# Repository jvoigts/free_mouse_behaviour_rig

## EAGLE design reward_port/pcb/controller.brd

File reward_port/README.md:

# DEPRECATED

free_mouse_behaviour_rig

i2c bus
reward port led
2 pushbuttons
nema 17 linear motor
IR led and reveicer
12V to 5V/3.3V regulators
some sort of beeper
attiny microcontroller attiny88 seems good

NEMA connector:
standard plug from 3d printer

Ring-topology connector:
GND
12VDC
i2c clk
i2c dat

Programming connector:

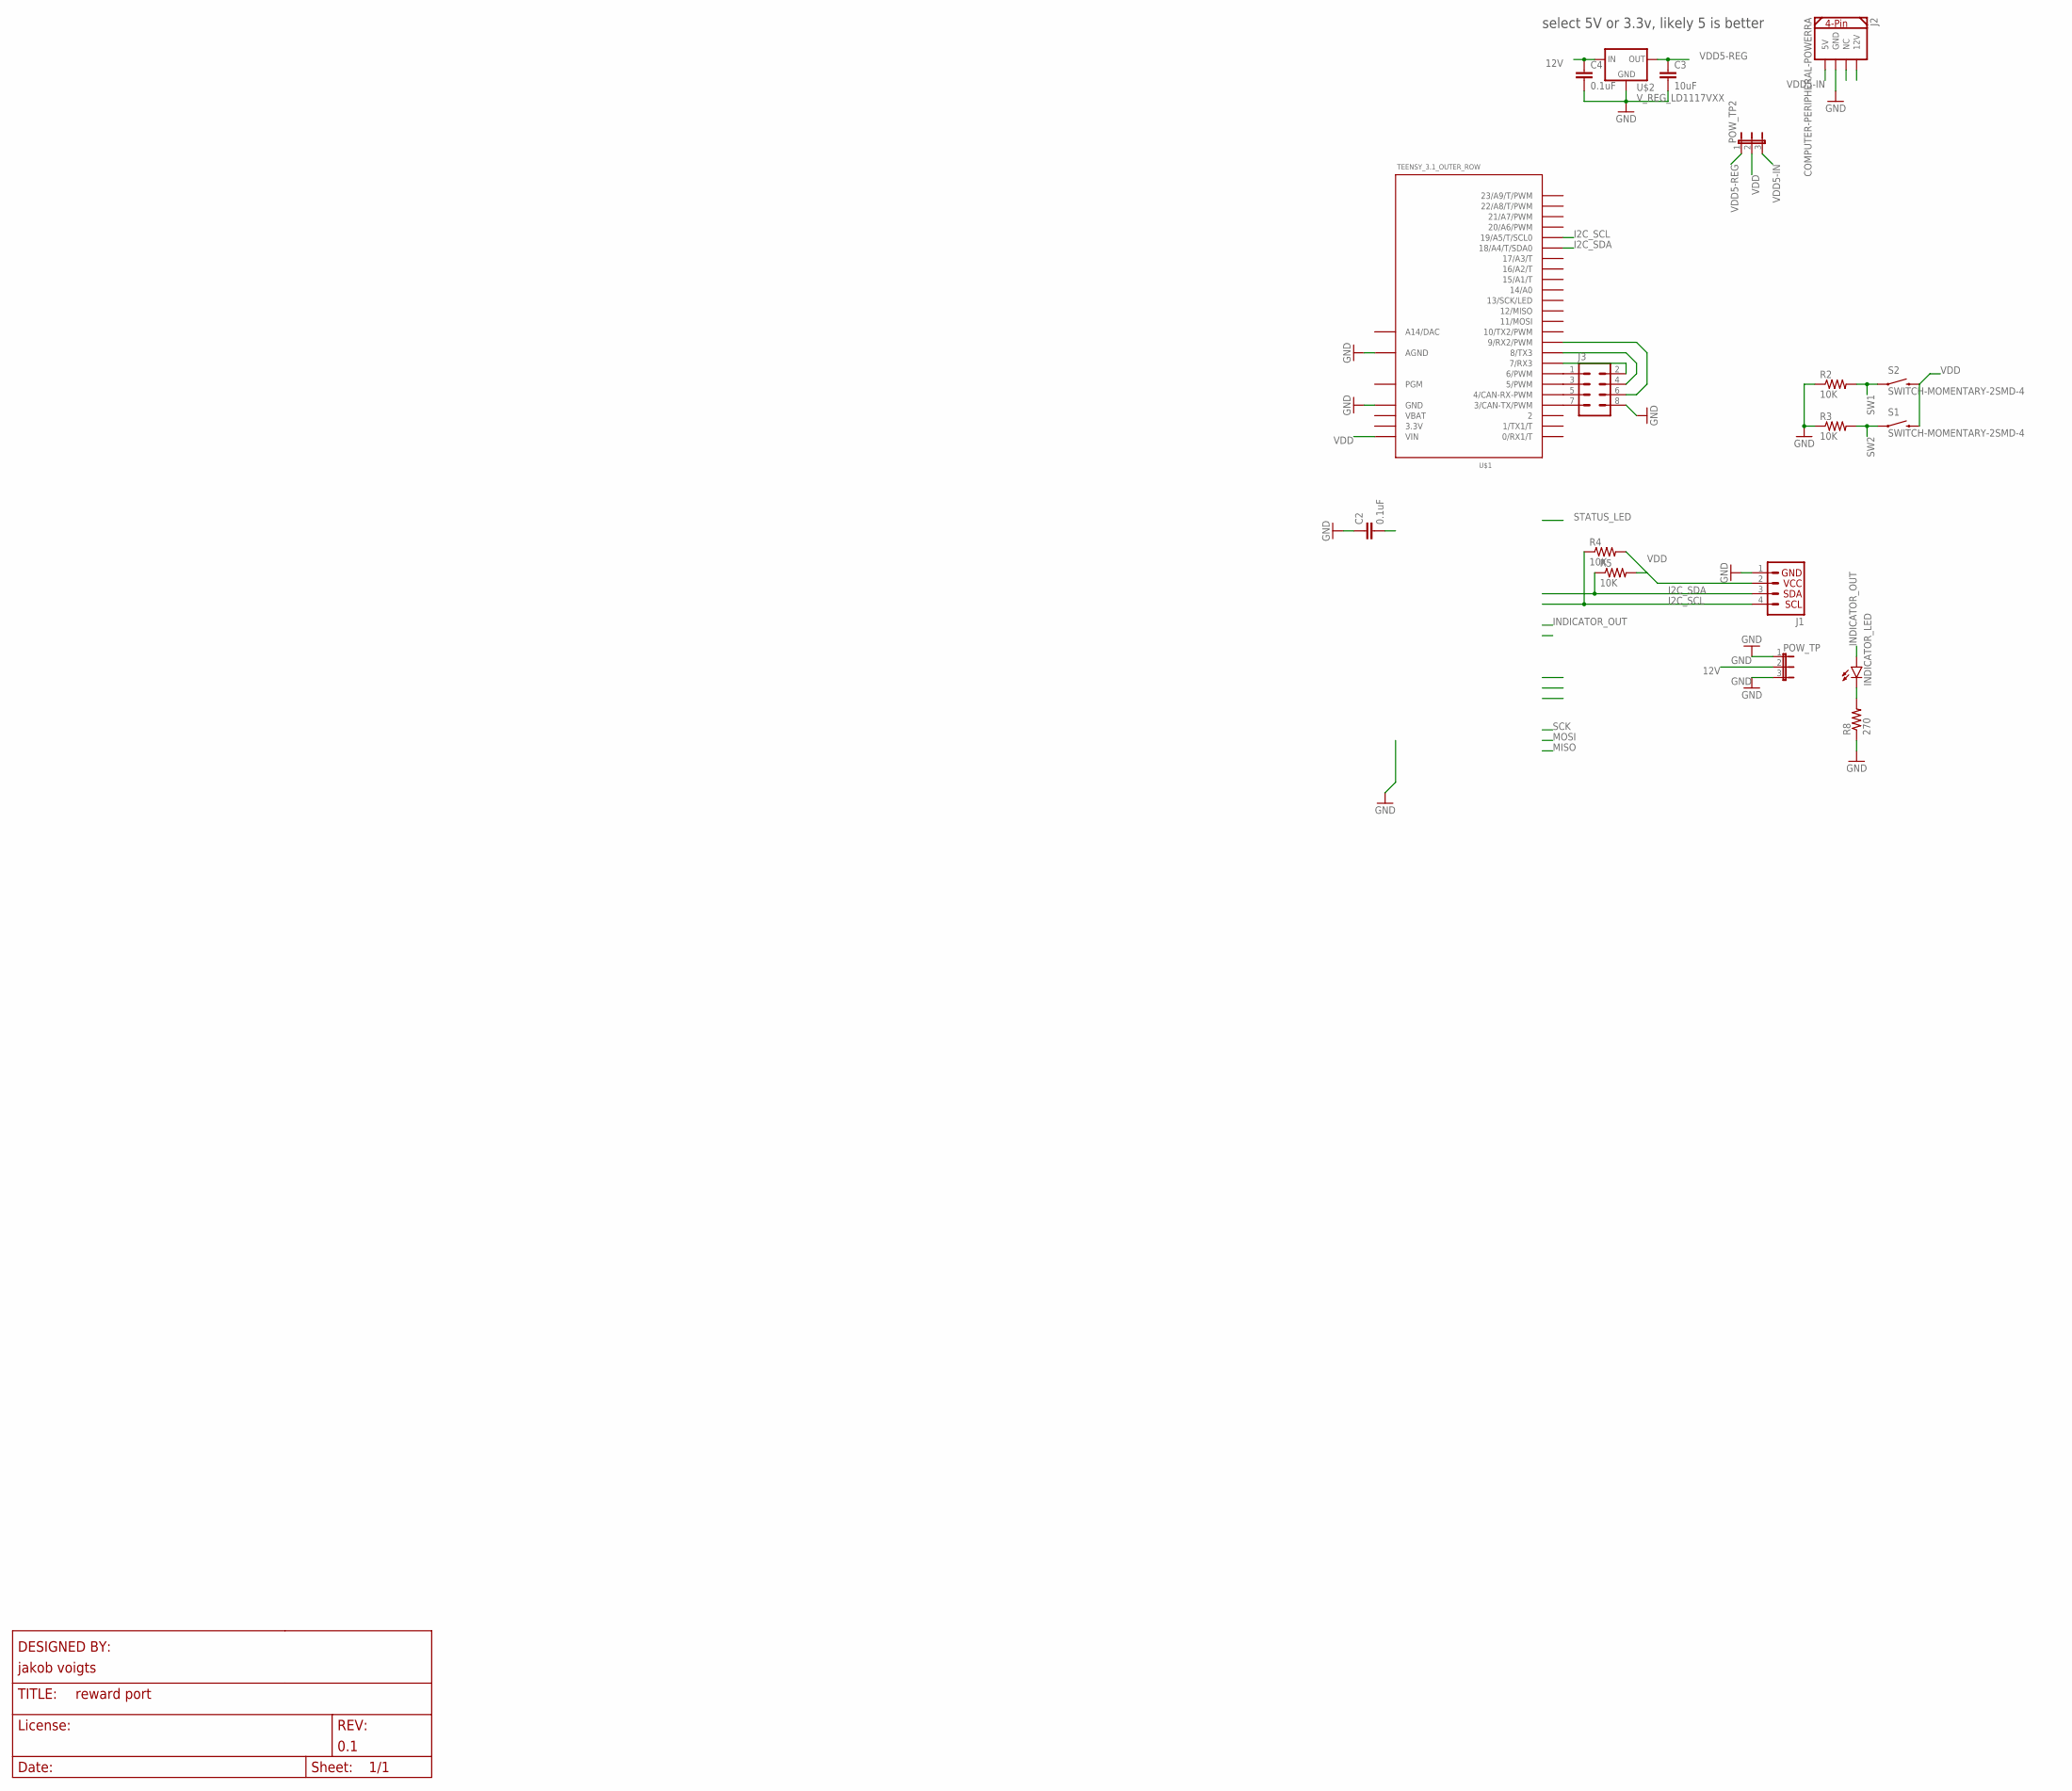
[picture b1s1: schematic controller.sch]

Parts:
C2, C4: 0.1uF; 0603-CAP
C3: 10uF; 0603-CAP
INDICATOR_LED: LED-3MM-NO_SILK; LED3MM-NS
J1: I2C_STANDARD; 1X04
J2: COMPUTER-PERIPHERAL-POWERRA; COMPUTER-PERIPHERAL-POWER-RA
J3: M04X2; 2X4
POW_TP, POW_TP2: JP3E; JP3
R2, R3, R4, R5: 10K; 0603-RES
R8: 270; 0603-RES
S1, S2: SWITCH-MOMENTARY-2SMD-4; TACTILE_SWITCH_TALL
U$1: TEENSY_3.1_OUTER_ROW; TEENSY3-OUTER_ROW
U$2: V_REG_LD1117VXX; 78XXL

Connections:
3.3V: U$1.3.3V, U$1.3.3V1 (3.3V)
12V: C4.1, POW_TP.2, U$2.OUT (IN)
GND: C2.1, C3.2, C4.2, J1.1, J2.GND, J3.8, POW_TP.1, POW_TP.3, R2.1, R3.1, R8.1, U$1.AGND, U$1.GND, U$1.GND1 (GND), U$2.IN (GND)
I2C_SCL: J1.4, R4.1, U$1.19/A5 (19/A5/T/SCL0)
I2C_SDA: J1.3, R5.1, U$1.18/A4 (18/A4/T/SDA0)
INDICATOR_OUT: INDICATOR_LED.A
unnamed: J3.1, U$1.6 (6/PWM)
unnamed: J3.3, U$1.5 (5/PWM)
unnamed: J3.5, U$1.4 (4/CAN-RX-PWM)
unnamed: J3.7, U$1.3 (3/CAN-TX/PWM)
unnamed: J3.2, U$1.7 (7/RX3)
unnamed: J3.4, U$1.8 (8/TX3)
unnamed: INDICATOR_LED.K (C), R8.2
unnamed: J3.6, U$1.9 (9/RX2/PWM)
SW1: R2.2, S2.A2 (1)
SW2: R3.2, S1.A2 (1)
VBAT: U$1.VBAT
VDD: J1.2, POW_TP2.2, R4.2, R5.2, S1.B2 (2), S2.B2 (2), U$1.VIN
VDD5-IN: J2.5V, POW_TP2.3
VDD5-REG: C3.1, POW_TP2.1, U$2.GND (OUT)

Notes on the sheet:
select 5V or 3.3v, likely 5 is better

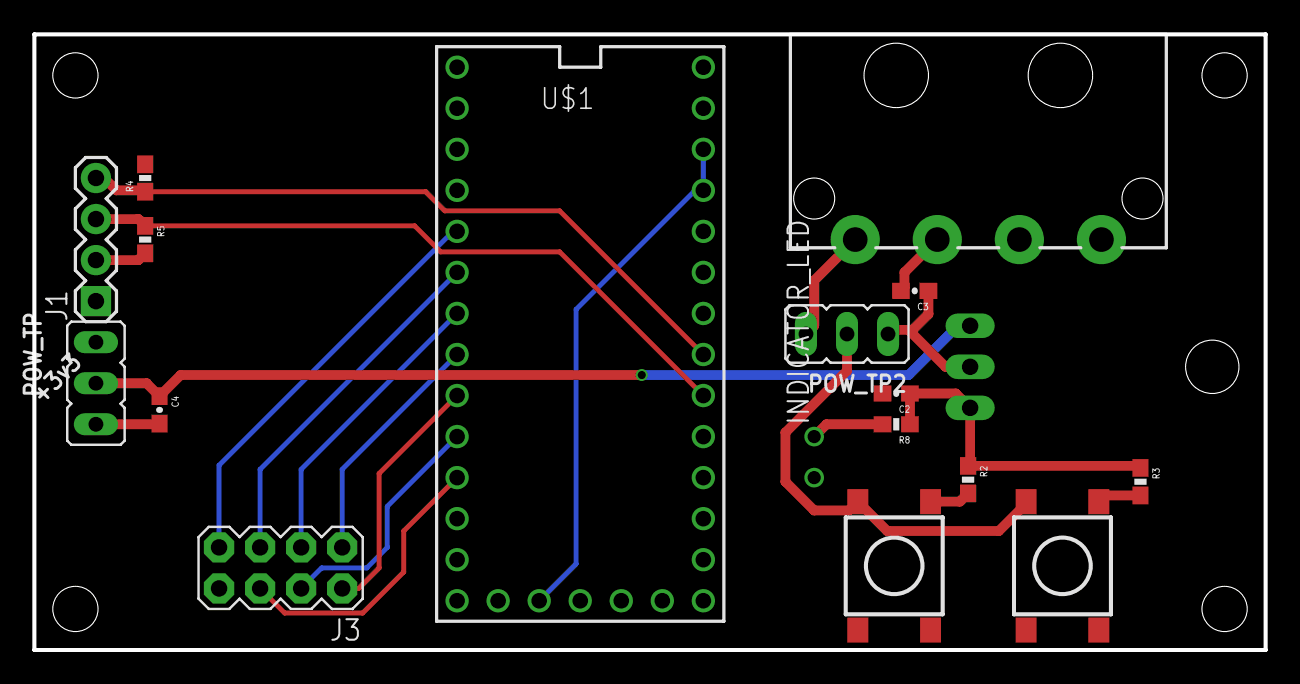
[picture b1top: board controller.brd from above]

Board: 4 copper layers, 76.2 x 38.1 mm, 18 parts (1 on the bottom side), 18 nets.

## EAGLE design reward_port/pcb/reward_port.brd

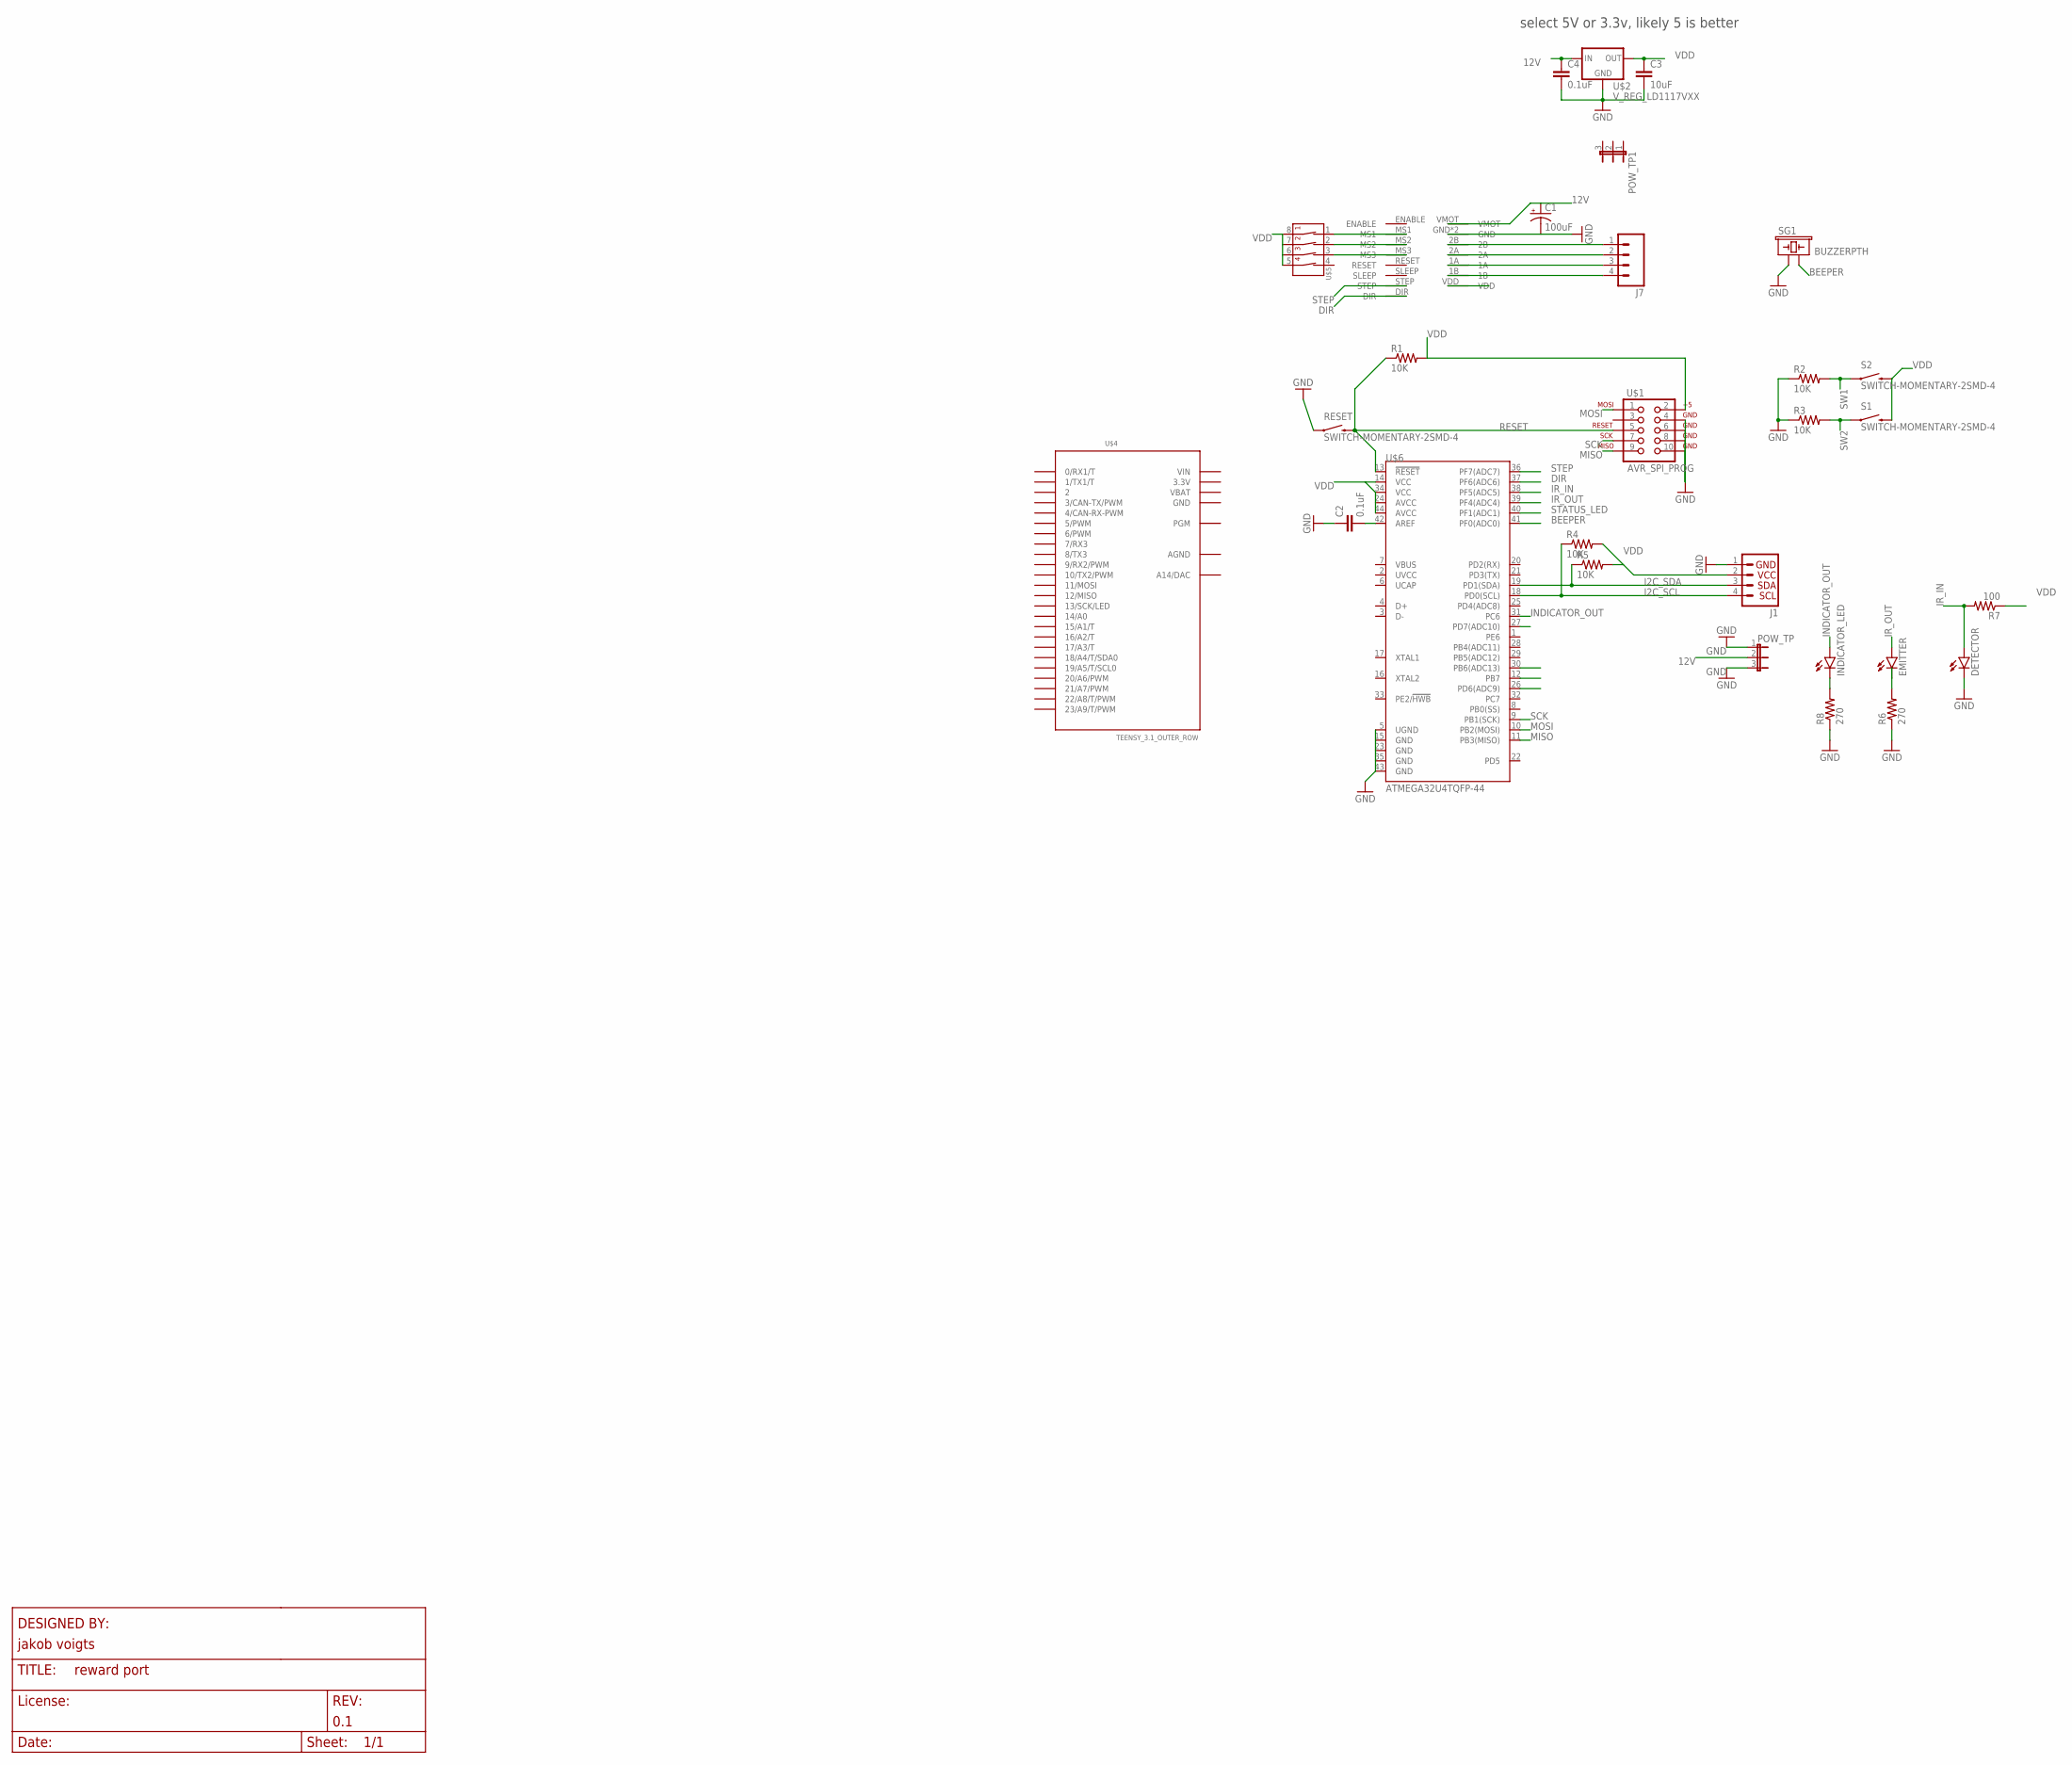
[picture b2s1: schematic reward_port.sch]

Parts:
C1: 100uF; EIA7343
C2, C4: 0.1uF; 0603-CAP
C3: 10uF; 0603-CAP
DETECTOR: LED-3MM-NO_SILK; LED3MM-NS
EMITTER: LED-3MM-NO_SILK; LED3MM-NS
INDICATOR_LED: LED-3MM-NO_SILK; LED3MM-NS
J1: I2C_STANDARD; 1X04
J7: M04POLAR; MOLEX-1X4
POW_TP, POW_TP1: JP3E; JP3
R1, R2, R3, R4, R5: 10K; 0603-RES
R6, R8: 270; 0603-RES
R7: 100; 0603-RES
RESET: SWITCH-MOMENTARY-2SMD-4; TACTILE_SWITCH_TALL
S1, S2: SWITCH-MOMENTARY-2SMD-4; TACTILE_SWITCH_TALL
SG1: BUZZERPTH; BUZZER-12MM
U$1: AVR_SPI_PROG; AVR_ICSP
U$2: V_REG_LD1117VXX; 78XXL
U$3: A4988
U$4: TEENSY_3.1_OUTER_ROW; TEENSY3-OUTER_ROW
U$5: 4-POS-DIP; 4-POS-DIP-SMD
U$6: ATMEGA32U4TQFP-44; TQFP44

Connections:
3.3V: U$4.3.3V, U$4.3.3V1 (3.3V)
12V: C1.A (+), C4.1, POW_TP.2, U$2.OUT (IN), U$3.VMOT
AGND: U$4.AGND
BEEPER: SG1.- (2), U$6.41 (PF0(ADC0))
DIR: U$3.DIR, U$6.37 (PF6(ADC6))
GND: C1.C (-), C2.1, C3.2, C4.2, DETECTOR.K (C), J1.1, POW_TP.1, POW_TP.3, R2.1, R3.1, R6.1, R8.1, RESET.A2 (1), SG1.+ (1), U$1.4, U$1.6, U$1.8, U$1.10, U$2.IN (GND), U$3.GND, U$3.GND2 (GND), U$4.GND, U$4.GND1 (GND), U$6.5 (UGND), U$6.15 (GND), U$6.23 (GND), U$6.35 (GND), U$6.43 (GND)
I2C_SCL: J1.4, R4.1, U$6.18 (PD0(SCL))
I2C_SDA: J1.3, R5.1, U$6.19 (PD1(SDA))
INDICATOR_OUT: INDICATOR_LED.A, U$6.31 (PC6)
IR_IN: DETECTOR.A, R7.2, U$6.38 (PF5(ADC5))
IR_OUT: EMITTER.A, U$6.39 (PF4(ADC4))
MISO: U$1.9, U$6.11 (PB3(MISO))
MOSI: U$1.1, U$6.10 (PB2(MOSI))
unnamed: J7.1, U$3.2B
unnamed: J7.2, U$3.2A
unnamed: J7.3, U$3.1A
unnamed: J7.4, U$3.1B
unnamed: U$3.MS1, U$5.1 (1A)
unnamed: U$3.MS2, U$5.2 (2A)
unnamed: U$3.MS3, U$5.3 (3A)
unnamed: C2.2, U$6.42 (AREF)
unnamed: INDICATOR_LED.K (C), R8.2
unnamed: EMITTER.K (C), R6.2
RESET: R1.1, RESET.B2 (2), U$1.5, U$6.13 (!RESET)
SCK: U$1.7, U$6.9 (PB1(SCK))
STATUS_LED: U$6.40 (PF1(ADC1))
STEP: U$3.STEP, U$6.36 (PF7(ADC7))
SW1: R2.2, S2.A2 (1)
SW2: R3.2, S1.A2 (1)
VBAT: U$4.VBAT
VDD: C3.1, J1.2, R1.2, R4.2, R5.2, R7.1, S1.B2 (2), S2.B2 (2), U$1.2, U$2.GND (OUT), U$3.VDD, U$5.5 (4B), U$5.6 (3B), U$5.7 (2B), U$5.8 (1B), U$6.14 (VCC), U$6.24 (AVCC), U$6.34 (VCC), U$6.44 (AVCC)
VIN: U$4.VIN

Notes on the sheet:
select 5V or 3.3v, likely 5 is better

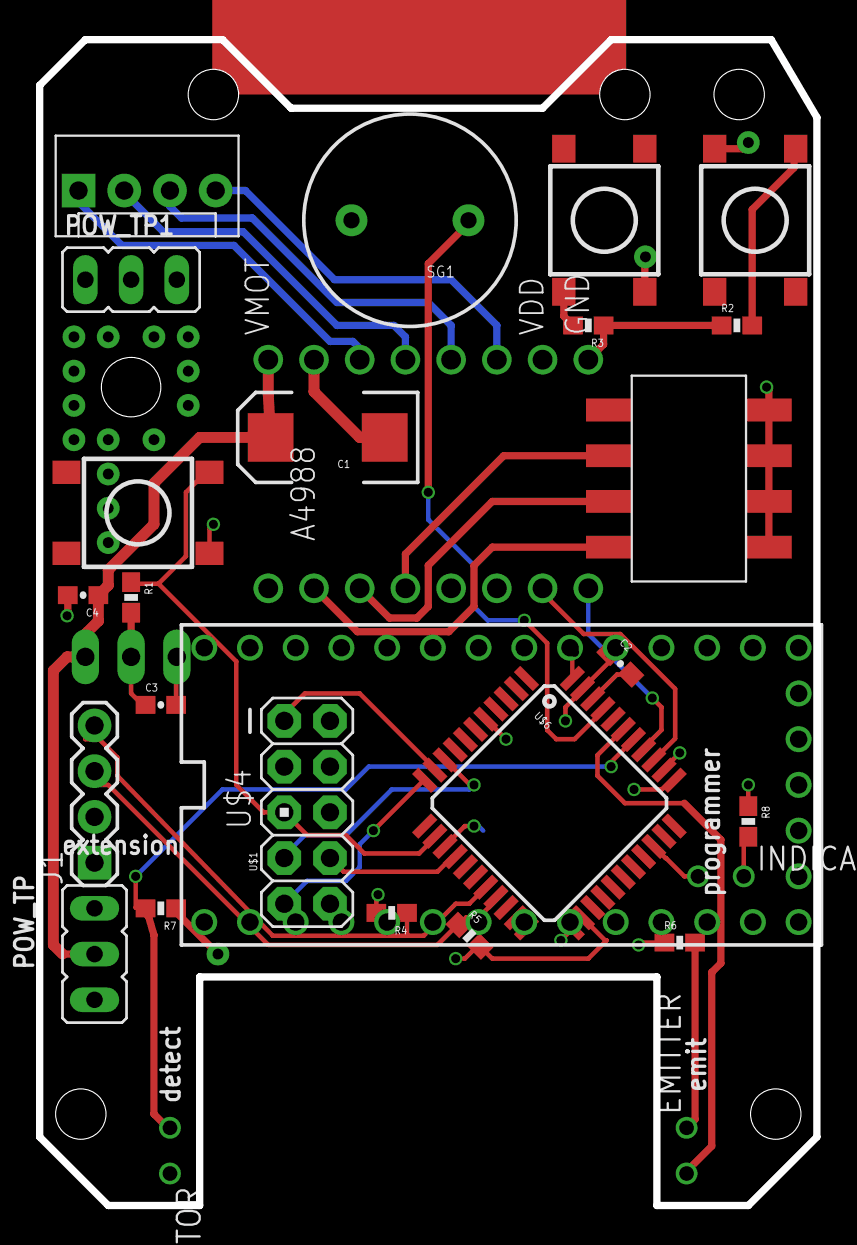
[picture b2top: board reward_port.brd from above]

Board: 4 copper layers, 43.2 x 64.8 mm, 29 parts (1 on the bottom side), 28 nets.

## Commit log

2016-08-08 added sparkfun libraries
2016-08-08 added motor driver to lib
2016-08-08 initial rough sizing
2016-08-08 bought parts list in ready
2016-08-09 more schematic layout
2016-08-09 added resistor lib
2016-08-09 replaced micro controller with attiny84
    needed Ain for LED thresholding
2016-08-09 went to atmega32 for i2c bus
    at this point the price is getting close to a teensy per port
2016-08-10 more layout and sch
2016-08-10 initial routing
2016-08-10 initial such controller board
2016-08-10 teensy libs
2016-08-10 controller routing
2016-08-10 test fit teensy
2016-08-19 added laser cut syringe pump test
2016-08-23 prototype draft for syringe pump
2016-08-24 moved files
2016-08-24 intial commit laser cut syringe pump
2016-08-24 added readme
2016-08-24 fixed file name
    thx windows
2016-08-24 added rendered image
    missing a bunch of components but illustrates the idea
2016-08-24 added more detailed model of 1ml syringe
2016-08-24 removed windows temp files
2016-08-24 renamed folder
2016-08-24 added rails
2016-08-24 syringe model update to current ver
2016-08-24 fixed spacer tab depth
    can now be stacked end-to-end
2016-08-24 fixed syringe holder tabs
2016-08-24 updated assembly with contraints
2016-08-24 added more parts
2016-08-24 increased clearance for stage compression bolt heads
    this way te M3x80 screws that hold the stage together can extend past
    the front plate
2016-08-24 added DXF files for laser cutting
2016-08-24 moved stuff aorund in assembly
2016-08-24 updates previews
2016-08-24 tiny assembly alignment fix
2016-08-24 added ponoko laser cut files
    these are for ponoko P2 sized acrylic, 3mm thick
    contains 2 sets of parts
    also added some extra spacers at odd smaller sizes for the carrier stack
2016-08-24 fixed line width for laser cutting
2016-08-24 various cleanups

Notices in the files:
parts and their libraries:
SparkFun-Electromechanical: Licensing: Creative Commons ShareAlike 4.0 International - https://creativecommons.org/licenses/by-sa/4.0
